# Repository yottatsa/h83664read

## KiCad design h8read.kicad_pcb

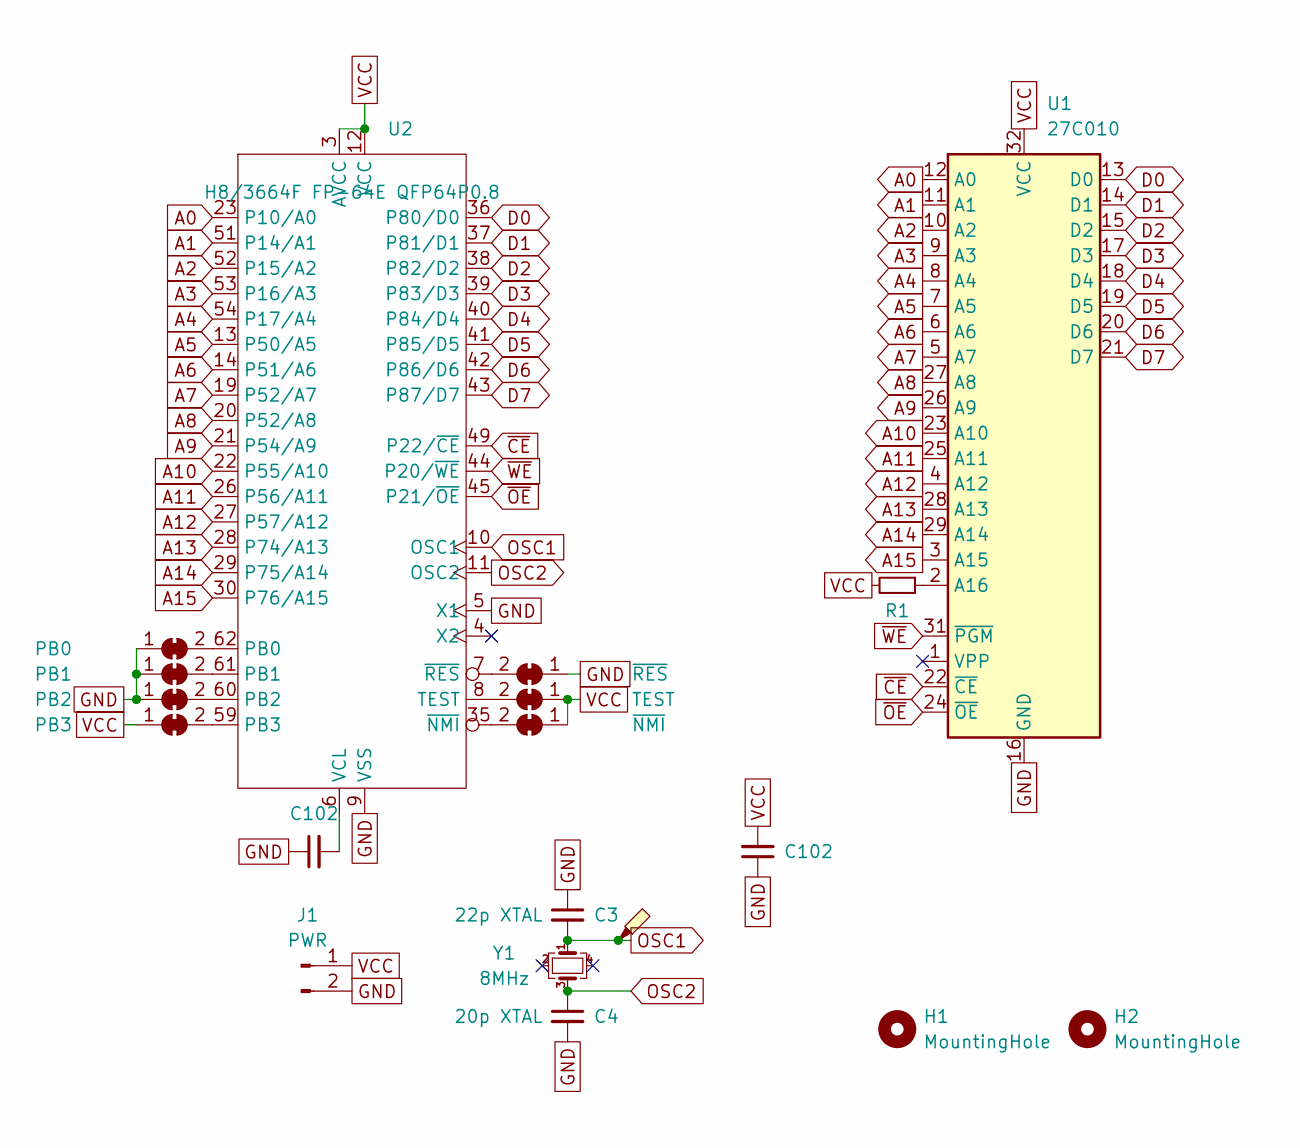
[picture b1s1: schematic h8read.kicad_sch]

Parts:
C3: 22p XTAL; C_0805_2012Metric_Pad1.18x1.45mm_HandSolder; Manufacturer_Part_Number C0805C220J1GACTU
C4: 20p XTAL; C_0805_2012Metric_Pad1.18x1.45mm_HandSolder; Manufacturer_Part_Number C0805C220J1GACTU
C102: PWR; C_1206_3216Metric_Pad1.33x1.80mm_HandSolder; Mouser Part Number 80-C1206X104G4HACTU
H1, H2: MountingHole; MountingHole_2.7mm_M2.5_DIN965
J1: PWR; PinHeader_1x02_P2.54mm_Vertical
JP1: PB3; SolderJumper-2_P1.3mm_Bridged_RoundedPad1.0x1.5mm
JP2: PB2; SolderJumper-2_P1.3mm_Bridged_RoundedPad1.0x1.5mm
JP3: PB1; SolderJumper-2_P1.3mm_Bridged_RoundedPad1.0x1.5mm
JP4: PB0; SolderJumper-2_P1.3mm_Bridged_RoundedPad1.0x1.5mm
JP5: ~{RES}; SolderJumper-2_P1.3mm_Bridged_RoundedPad1.0x1.5mm
JP6: TEST; SolderJumper-2_P1.3mm_Bridged_RoundedPad1.0x1.5mm
JP7: ~{NMI}; SolderJumper-2_P1.3mm_Bridged_RoundedPad1.0x1.5mm
R1: A16; R_1206_3216Metric_Pad1.30x1.75mm_HandSolder; Mouser Part Number 71-RCC120620K0FKEA
TP1: XTAL; TestPoint_Pad_1.0x1.0mm
U1: 27C010; DIP-32_W7.62mm
U2: H8/3664F FP-64E QFP64P0.8; TQFP-64_14x14mm_P0.8mm
Y1: 8MHz; Crystal_SMD_5032-4Pin_5.0x3.2mm

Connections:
A0: U1.12 (A0), U2.23 (P10/A0)
A1: U1.11 (A1), U2.51 (P14/A1)
A2: U1.10 (A2), U2.52 (P15/A2)
A3: U1.9 (A3), U2.53 (P16/A3)
A4: U1.8 (A4), U2.54 (P17/A4)
A5: U1.7 (A5), U2.13 (P50/A5)
A6: U1.6 (A6), U2.14 (P51/A6)
A7: U1.5 (A7), U2.19 (P52/A7)
A8: U1.27 (A8), U2.20 (P52/A8)
A9: U1.26 (A9), U2.21 (P54/A9)
A10: U1.23 (A10), U2.22 (P55/A10)
A11: U1.25 (A11), U2.26 (P56/A11)
A12: U1.4 (A12), U2.27 (P57/A12)
A13: U1.28 (A13), U2.28 (P74/A13)
A14: U1.29 (A14), U2.29 (P75/A14)
A15: U1.3 (A15), U2.30 (P76/A15)
D0: U1.13 (D0), U2.36 (P80/D0)
D1: U1.14 (D1), U2.37 (P81/D1)
D2: U1.15 (D2), U2.38 (P82/D2)
D3: U1.17 (D3), U2.39 (P83/D3)
D4: U1.18 (D4), U2.40 (P84/D4)
D5: U1.19 (D5), U2.41 (P85/D5)
D6: U1.20 (D6), U2.42 (P86/D6)
D7: U1.21 (D7), U2.43 (P87/D7)
GND: C3.1, C4.2, J1.2, JP2.1 (A), JP3.1 (A), JP4.1 (A), JP5.1 (A), U1.16 (GND), U2.5 (X1), U2.9 (VSS); also elsewhere on the board
unnamed: JP1.2 (B), U2.59 (PB3)
unnamed: JP2.2 (B), U2.60 (PB2)
unnamed: JP3.2 (B), U2.61 (PB1)
unnamed: JP4.2 (B), U2.62 (PB0)
unnamed: JP5.2 (B), U2.7 (~RES)
unnamed: JP6.2 (B), U2.8 (TEST)
unnamed: JP7.2 (B), U2.35 (~NMI)
unnamed: R1.1, U1.2 (A16)
unnamed 33: U2.6 (VCL); also elsewhere on the board
OSC1: C3.2, TP1.1, U2.10 (OSC1), Y1.1
OSC2: C4.1, U2.11 (OSC2), Y1.3
VCC: J1.1, JP1.1 (A), JP6.1 (A), JP7.1 (A), R1.2, U1.32 (VCC), U2.3 (AVCC), U2.12 (VCC); also elsewhere on the board
~CE: U1.22 (~CE), U2.49 (P22/~CE)
~OE: U1.24 (~OE), U2.45 (P21/~OE)
~WE: U1.31 (~PGM), U2.44 (P20/~WE)

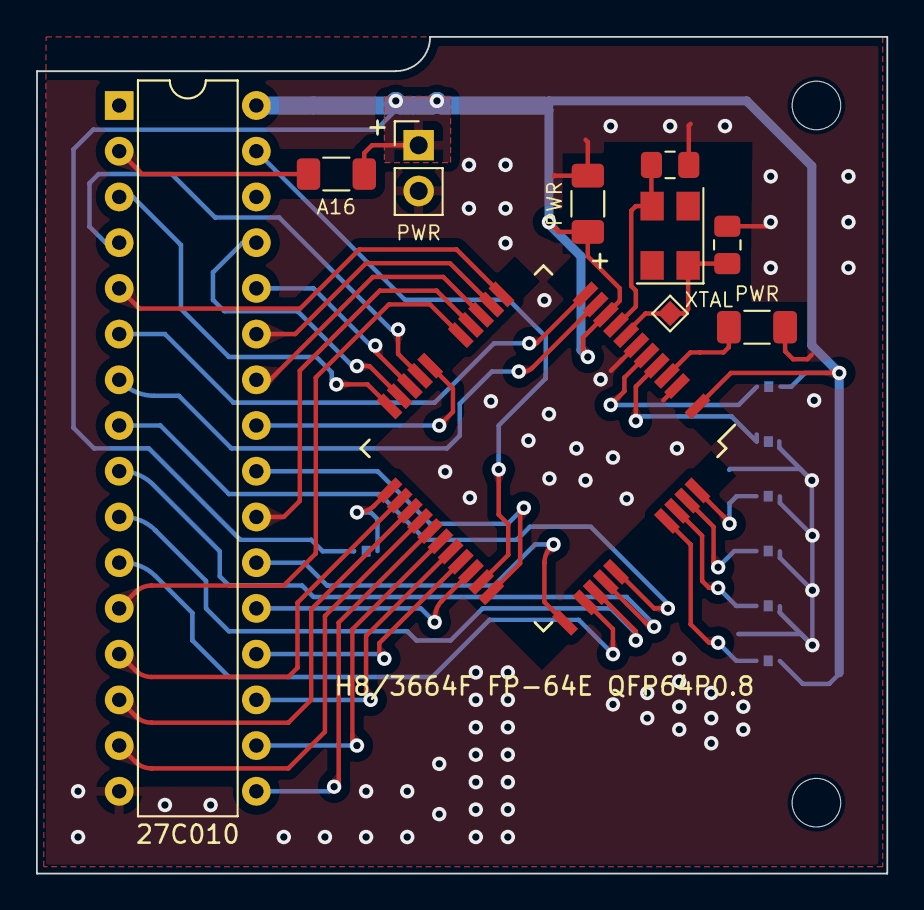
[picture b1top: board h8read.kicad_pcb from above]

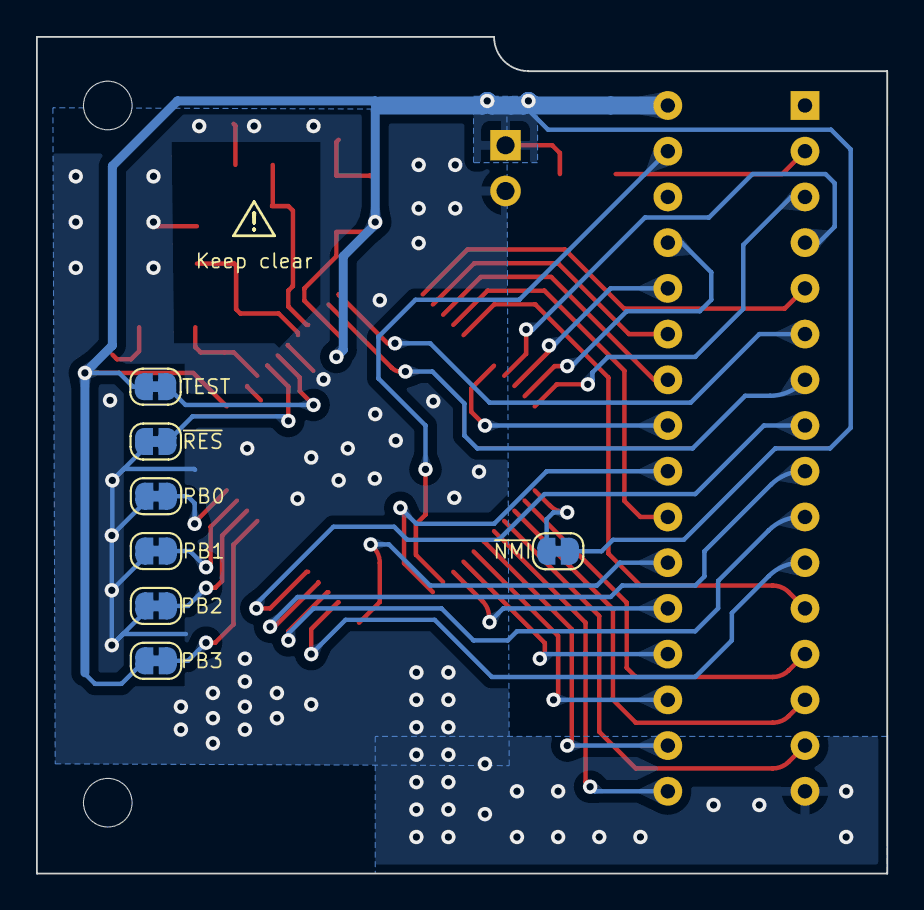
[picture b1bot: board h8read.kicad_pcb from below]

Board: 2 copper layers, 47.2 x 46.5 mm, 19 parts (7 on the bottom side), 40 nets.

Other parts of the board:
C1, C2: PWR; C_1206_3216Metric_Pad1.33x1.80mm_HandSolder

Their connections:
GND: C1.1, C2.1; also elsewhere on the board
unnamed 33: C1.2; also elsewhere on the board
VCC: C2.2; also elsewhere on the board

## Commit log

2024-04-30 initial
2024-04-30 r1 gerbers
2024-05-01 second revision
